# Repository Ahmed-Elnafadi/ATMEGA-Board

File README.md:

# ATMEGA-Board
Developed ATMEGA board for Embedded System Engineers using KiCad Software. 

# Real Product after Manufacturing and Assembling:

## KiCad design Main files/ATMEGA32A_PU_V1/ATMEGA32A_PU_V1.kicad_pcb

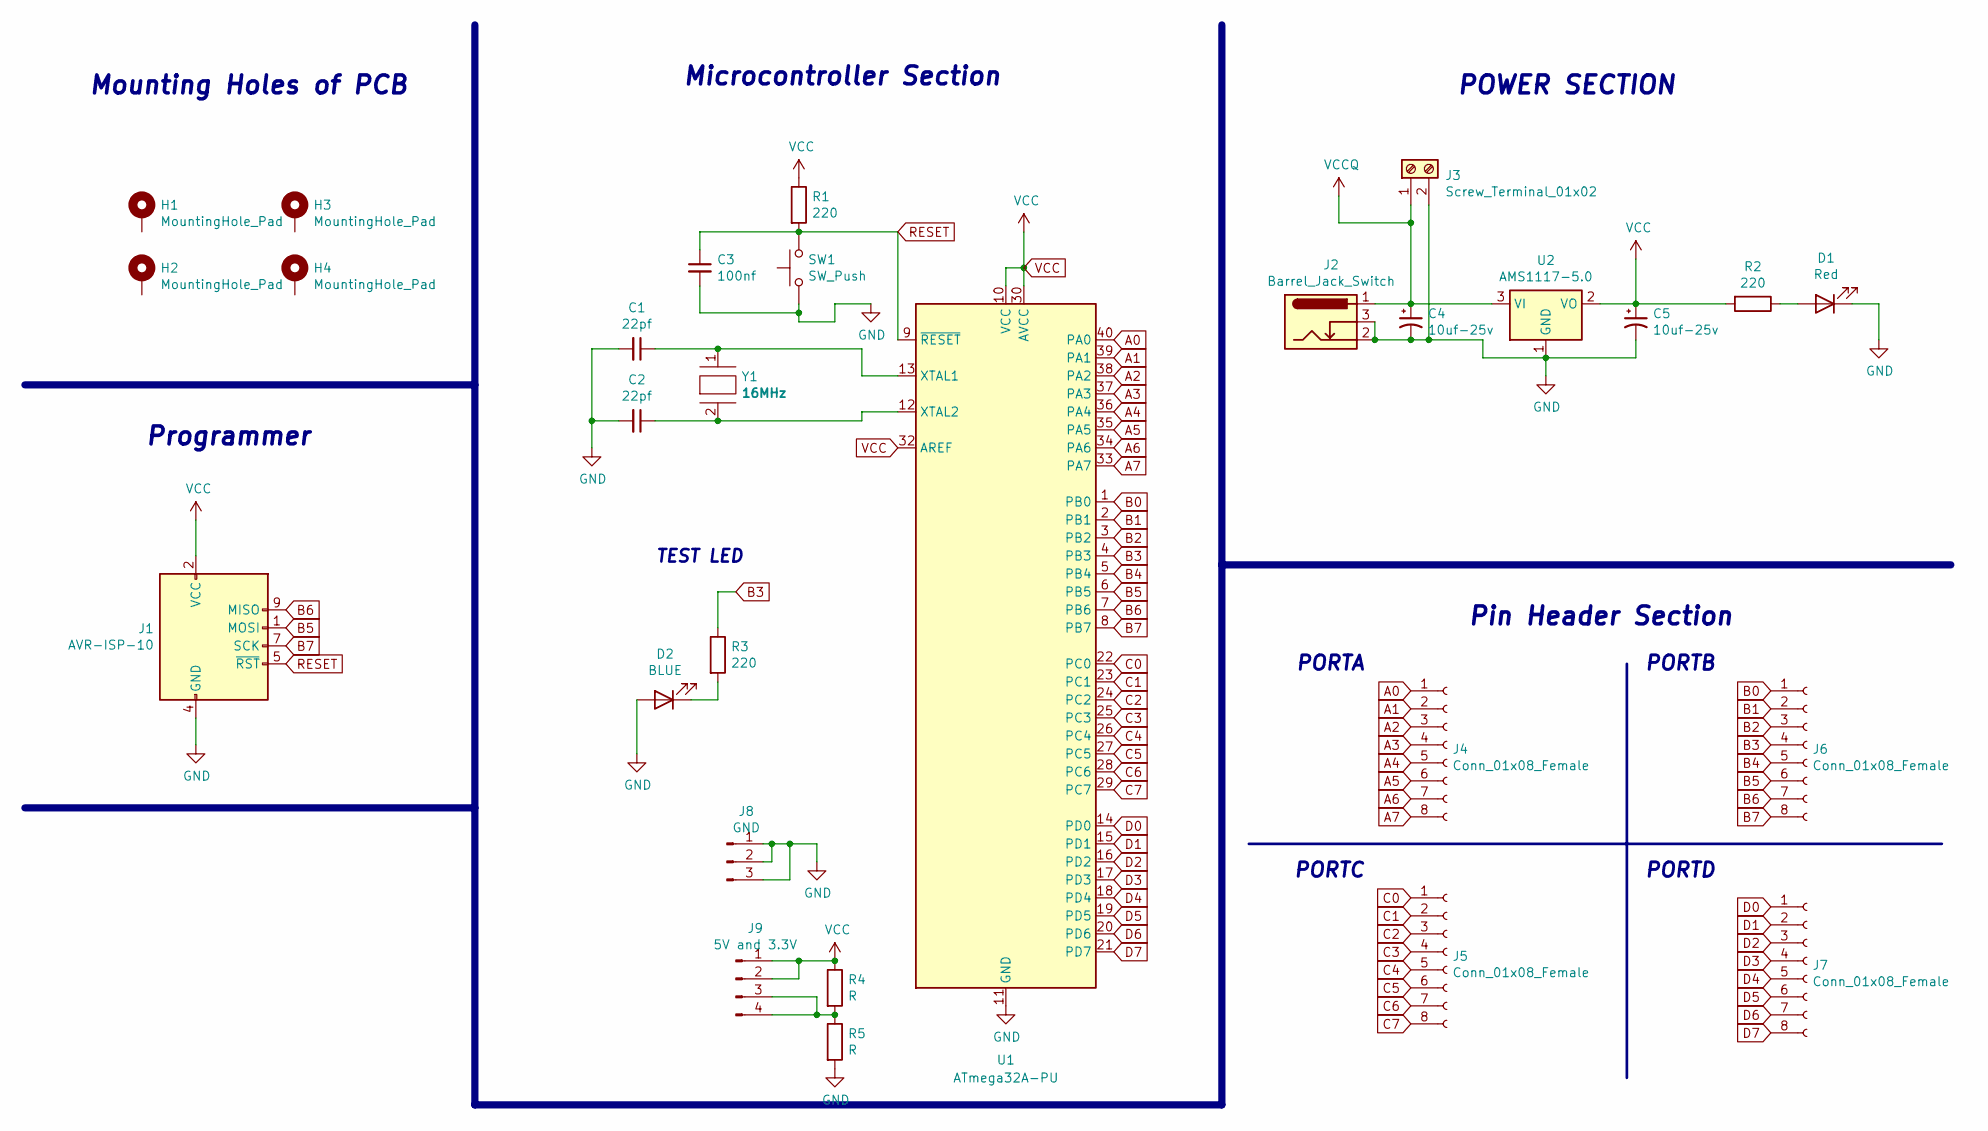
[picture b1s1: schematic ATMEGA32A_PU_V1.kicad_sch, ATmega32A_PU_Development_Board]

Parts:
C1, C2: 22pf; C_0805_2012Metric_Pad1.18x1.45mm_HandSolder
C3: 100nf; C_0805_2012Metric_Pad1.18x1.45mm_HandSolder
C4, C5: 10uf-25v; CP_Elec_5x5.3
D1: Red; LED_0603_1608Metric_Pad1.05x0.95mm_HandSolder
D2: BLUE; LED_0603_1608Metric_Pad1.05x0.95mm_HandSolder
H1, H2, H3, H4: MountingHole_Pad; MountingHole_4mm_Pad_Via
J1: AVR-ISP-10; IDC-Header_2x05_P2.54mm_Vertical
J2: Barrel_Jack_Switch; BarrelJack_Wuerth_6941xx301002
J3: Screw_Terminal_01x02; TerminalBlock_Phoenix_MKDS-1,5-2_1x02_P5.00mm_Horizontal
J4, J5, J6, J7: Conn_01x08_Female; PinHeader_1x08_P2.54mm_Vertical
J8: GND; PinHeader_1x03_P2.54mm_Vertical
J9: 5V and 3.3V; PinHeader_1x04_P2.54mm_Vertical
R1, R2, R3: 220; R_1206_3216Metric_Pad1.30x1.75mm_HandSolder
R4, R5: R; R_1206_3216Metric_Pad1.30x1.75mm_HandSolder
SW1: SW_Push; SW_PUSH_6mm
U1: ATmega32A-PU; DIP-40_W15.24mm
U2: AMS1117-5.0; SOT-223-3_TabPin2
Y1: 16MHz; Crystal_HC49-4H_Vertical

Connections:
A0: J4.1, U1.40 (PA0)
A1: J4.2, U1.39 (PA1)
A2: J4.3, U1.38 (PA2)
A3: J4.4, U1.37 (PA3)
A4: J4.5, U1.36 (PA4)
A5: J4.6, U1.35 (PA5)
A6: J4.7, U1.34 (PA6)
A7: J4.8, U1.33 (PA7)
B0: J6.1, U1.1 (PB0)
B1: J6.2, U1.2 (PB1)
B2: J6.3, U1.3 (PB2)
B3: J6.4, R3.1, U1.4 (PB3)
B4: J6.5, U1.5 (PB4)
B5: J1.1 (MOSI), J6.6, U1.6 (PB5)
B6: J1.9 (MISO), J6.7, U1.7 (PB6)
B7: J1.7 (SCK), J6.8, U1.8 (PB7)
C0: J5.1, U1.22 (PC0)
C1: J5.2, U1.23 (PC1)
C2: J5.3, U1.24 (PC2)
C3: J5.4, U1.25 (PC3)
C4: J5.5, U1.26 (PC4)
C5: J5.6, U1.27 (PC5)
C6: J5.7, U1.28 (PC6)
C7: J5.8, U1.29 (PC7)
D0: J7.1, U1.14 (PD0)
D1: J7.2, U1.15 (PD1)
D2: J7.3, U1.16 (PD2)
D3: J7.4, U1.17 (PD3)
D4: J7.5, U1.18 (PD4)
D5: J7.6, U1.19 (PD5)
D6: J7.7, U1.20 (PD6)
D7: J7.8, U1.21 (PD7)
GND: C1.2, C2.2, C3.2, C4.2, C5.2, D1.1 (K), D2.2 (A), J1.4 (GND), J1.6 (GND), J1.8 (GND), J1.10 (GND), J2.2, J2.3, J3.2, J8.1, J8.2, J8.3, R5.2, SW1.1, U1.11 (GND), U1.31 (GND), U2.1 (GND)
unnamed: C1.1, U1.13 (XTAL1), Y1.1
unnamed: C2.1, U1.12 (XTAL2), Y1.2
unnamed: D1.2 (A), R2.1
unnamed: D2.1 (K), R3.2
unnamed: J9.3, J9.4, R4.2, R5.1
RESET: C3.1, J1.5 (~RST), R1.2, SW1.2, U1.9 (~RESET)
VCC: C5.1, J1.2 (VCC), J9.1, J9.2, R1.1, R2.2, R4.1, U1.10 (VCC), U1.30 (AVCC), U1.32 (AREF), U2.2 (VO)
VCCQ: C4.1, J2.1, J3.1, U2.3 (VI)

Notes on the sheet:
PORTA
PORTB
PORTC
TEST LED
Pin Header Section
Microcontroller Section
Mounting Holes of PCB
Programmer
PORTD
POWER SECTION

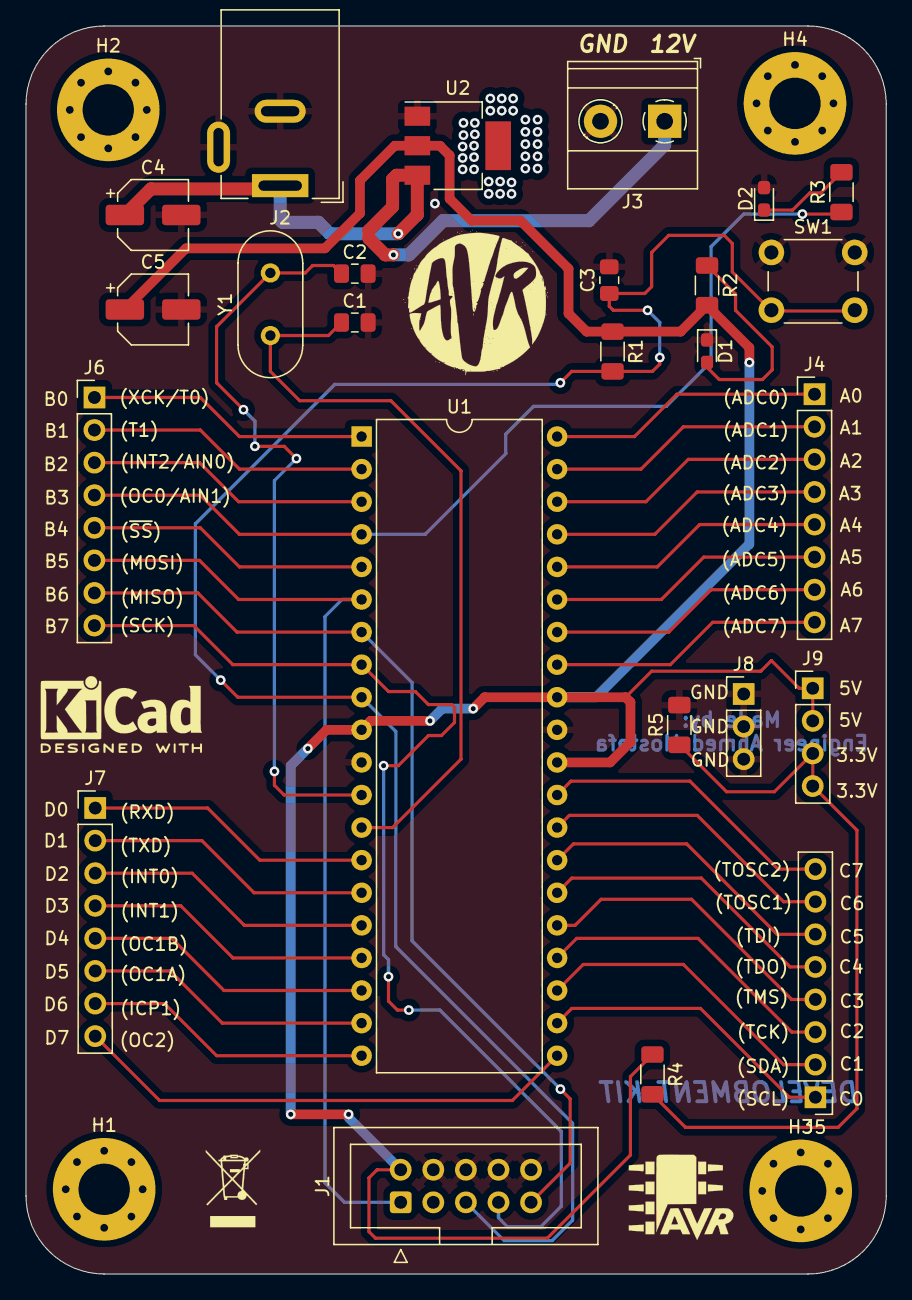
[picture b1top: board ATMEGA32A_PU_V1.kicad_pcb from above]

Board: 2 copper layers, 67.1 x 97.3 mm, 29 parts (0 on the bottom side), 41 nets.

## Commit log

2024-07-05 Add PCB Files to remote repo.
